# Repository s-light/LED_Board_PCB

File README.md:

# LED_Board_PCB

small round PCB with TI TLC5971 12ch 16bit LED-driver and NICHIA NSSM124AT RGB-LED.  
(originaly designed for Lumifluidus Prototyp)

<!-- file format / software information -->
## used software:  
    Application: kicad  
    Version: (2014-12-26 BZR 5338)-product Release build  
    wxWidgets: Version 3.0.0 (debug,wchar_t,compiler with C++ ABI 1002,GCC 4.8.2,wx containers,compatible with 2.8)    
    Platform: Windows 7 (build 7601, Service Pack 1), 64-bit edition, 64 bit, Little endian, wxMSW  
    Boost version: 1.54.0  
        USE_WX_GRAPHICS_CONTEXT=OFF  
        USE_WX_OVERLAY=OFF  
        KICAD_SCRIPTING=ON  
        KICAD_SCRIPTING_MODULES=ON  
        KICAD_SCRIPTING_WXPYTHON=ON  
        USE_FP_LIB_TABLE=HARD_CODED_ON  
        BUILD_GITHUB_PLUGIN=ON
    Inkscape 0.91 r13725

<!-- License info -->
   
LED Board PCB by [Stefan Krüger (s-light)](https://github.com/s-light/LED_Board_PCB) is licensed under a  
[Creative Commons Attribution 4.0 International License](http://creativecommons.org/licenses/by/4.0/).

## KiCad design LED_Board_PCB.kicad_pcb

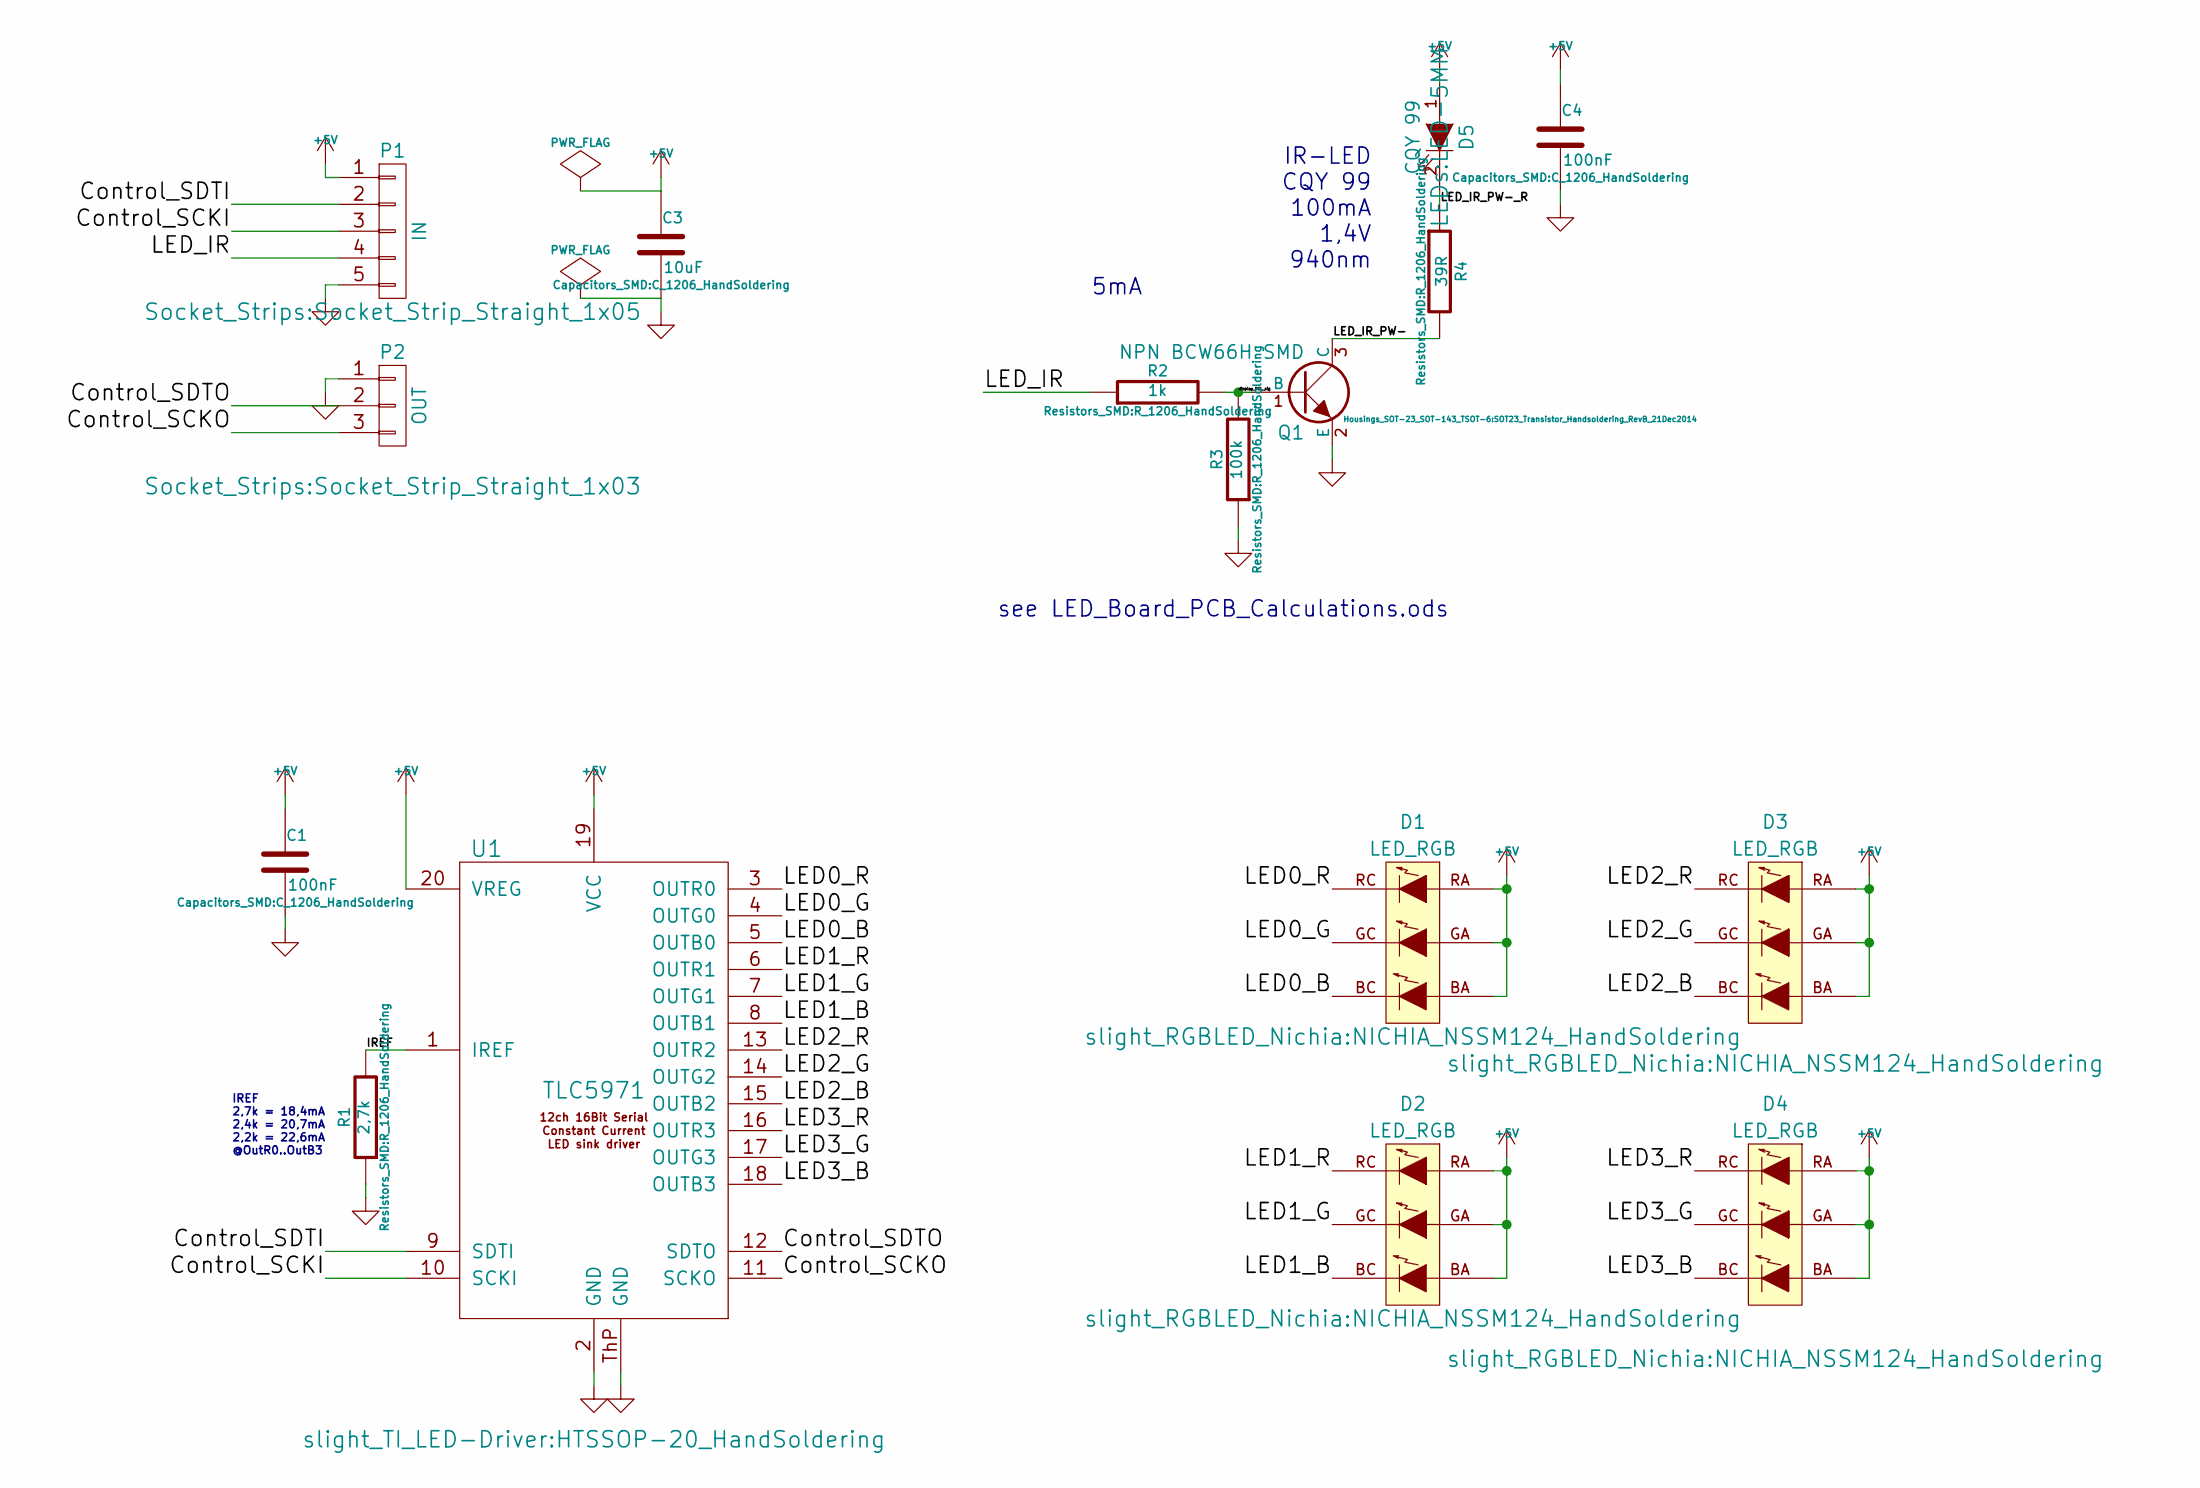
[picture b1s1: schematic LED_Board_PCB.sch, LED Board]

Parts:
C1, C4: 100nF; C_1206_HandSoldering
C3: 10uF; C_1206_HandSoldering
D1, D2, D3, D4: LED_RGB; NICHIA_NSSM124_HandSoldering
D5: CQY 99; LED-5MM
P1: IN; Socket_Strip_Straight_1x05
P2: OUT; Socket_Strip_Straight_1x03
Q1: NPN BCW66H SMD; SOT23_Transistor_Handsoldering_RevB_21Dec2014
R1: 2,7k; R_1206_HandSoldering
R2: 1k; R_1206_HandSoldering
R3: 100k; R_1206_HandSoldering
R4: 39R; R_1206_HandSoldering
U1: TLC5971; HTSSOP-20_HandSoldering

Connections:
+5V: C1.1, C3.1, C4.1, D1.BA (BLUE_ANODE), D1.GA (GREEN_ANODE), D1.RA (RED_ANODE), D2.BA (BLUE_ANODE), D2.GA (GREEN_ANODE), D2.RA (RED_ANODE), D3.BA (BLUE_ANODE), D3.GA (GREEN_ANODE), D3.RA (RED_ANODE), D4.BA (BLUE_ANODE), D4.GA (GREEN_ANODE), D4.RA (RED_ANODE), D5.1 (A), P1.1, U1.19 (VCC), U1.20 (VREG)
/Control_SCKI: P1.3, U1.10 (SCKI)
/Control_SCKO: P2.3, U1.11 (SCKO)
/Control_SDTI: P1.2, U1.9 (SDTI)
/Control_SDTO: P2.2, U1.12 (SDTO)
/IREF: R1.2, U1.1 (IREF)
/LED0_B: D1.BC (BLUE_CATHODE), U1.5 (OUTB0)
/LED0_G: D1.GC (GREEN_CATHODE), U1.4 (OUTG0)
/LED0_R: D1.RC (RED_CATHODE), U1.3 (OUTR0)
/LED1_B: D2.BC (BLUE_CATHODE), U1.8 (OUTB1)
/LED1_G: D2.GC (GREEN_CATHODE), U1.7 (OUTG1)
/LED1_R: D2.RC (RED_CATHODE), U1.6 (OUTR1)
/LED2_B: D3.BC (BLUE_CATHODE), U1.15 (OUTB2)
/LED2_G: D3.GC (GREEN_CATHODE), U1.14 (OUTG2)
/LED2_R: D3.RC (RED_CATHODE), U1.13 (OUTR2)
/LED3_B: D4.BC (BLUE_CATHODE), U1.18 (OUTB3)
/LED3_G: D4.GC (GREEN_CATHODE), U1.17 (OUTG3)
/LED3_R: D4.RC (RED_CATHODE), U1.16 (OUTR3)
/LED_IR: P1.4, R2.1
/LED_IR_PW-: Q1.3 (C), R4.2
/LED_IR_PW-_R: D5.2 (K), R4.1
/display_BGL_sig: Q1.1 (B), R2.2, R3.2
GND: C1.2, C3.2, C4.2, P1.5, P2.1, Q1.2 (E), R1.1, R3.1, U1.2 (GND), U1.ThP (GND)

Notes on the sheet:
see LED_Board_PCB_Calculations.ods
IR-LED CQY 99 100mA 1,4V 940nm
5mA
IREF 2,7k = 18,4mA 2,4k = 20,7mA 2,2k = 22,6mA @OutR0..OutB3

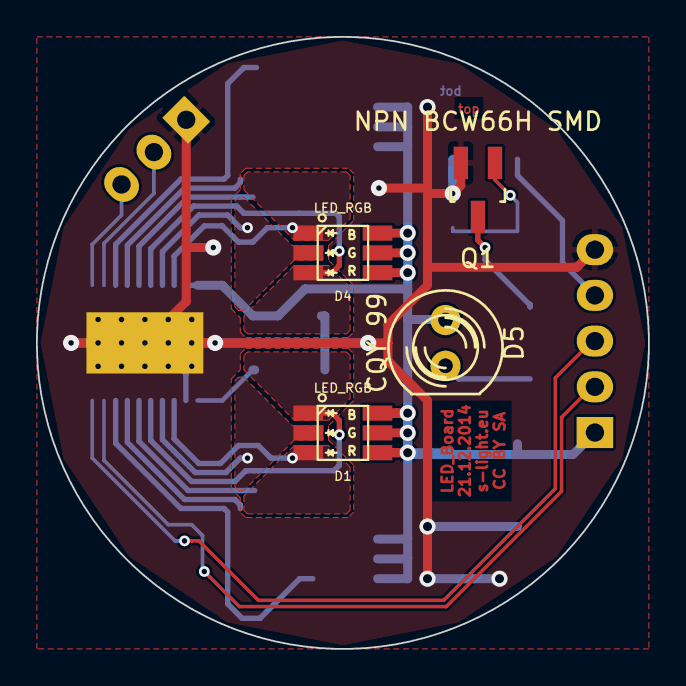
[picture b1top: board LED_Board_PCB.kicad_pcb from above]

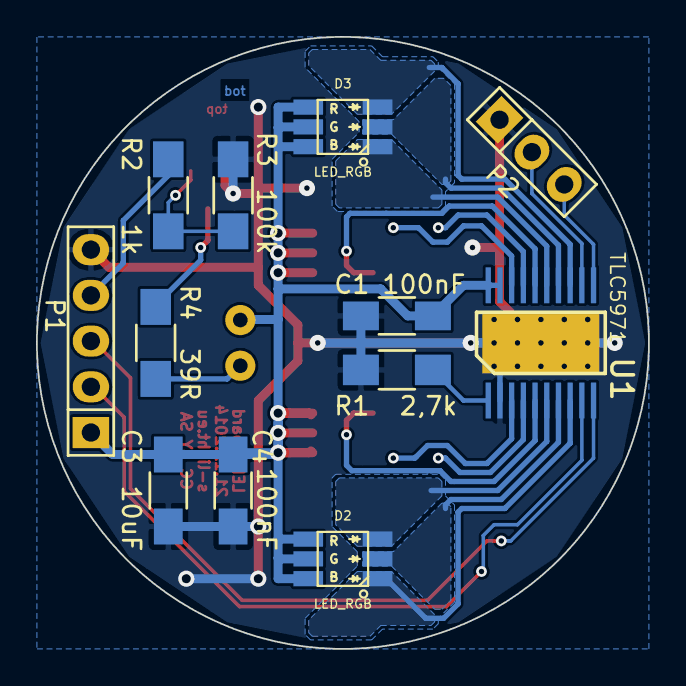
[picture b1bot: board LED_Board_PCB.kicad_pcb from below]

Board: 2 copper layers, 34.0 x 34.0 mm, 16 parts (12 on the bottom side), 23 nets.

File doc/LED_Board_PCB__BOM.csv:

"Id";"Designator";"Package";"Quantity";"Designation";"Supplier and ref";
1;"D5";"LED-5MM";1;"CQY 99";;;
2;"C1,C4";"C_1206_HandSoldering";2;"100nF";;;
3;"R1";"R_1206_HandSoldering";1;"2,7k";;;
4;"R2";"R_1206_HandSoldering";1;"1k";;;
5;"C3";"C_1206_HandSoldering";1;"10uF";;;
6;"R3";"R_1206_HandSoldering";1;"100k";;;
7;"R4";"R_1206_HandSoldering";1;"39R";;;
8;"P1";"Socket_Strip_Straight_1x05";1;"IN";;;
9;"P2";"Socket_Strip_Straight_1x03";1;"OUT";;;
10;"D1,D2,D3,D4";"NICHIA_NSSM124_HandSoldering";4;"LED_RGB";;;
11;"U1";"HTSSOP-20_HandSoldering";1;"TLC5971";;;
12;"Q1";"SOT23_Transistor_Handsoldering_RevB_21Dec2014";1;"NPN BCW66H SMD";;;

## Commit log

2016-01-13 migrated to git
2016-01-13 added images
2016-01-13 fixed license formating
2017-07-27 added PinInfo image to readme
2017-07-27 :sunrise: fixed image in readme

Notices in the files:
LED_Board_PCB.kicad_pcb:
CC BY SA
README.md:
CC BY 4.0
